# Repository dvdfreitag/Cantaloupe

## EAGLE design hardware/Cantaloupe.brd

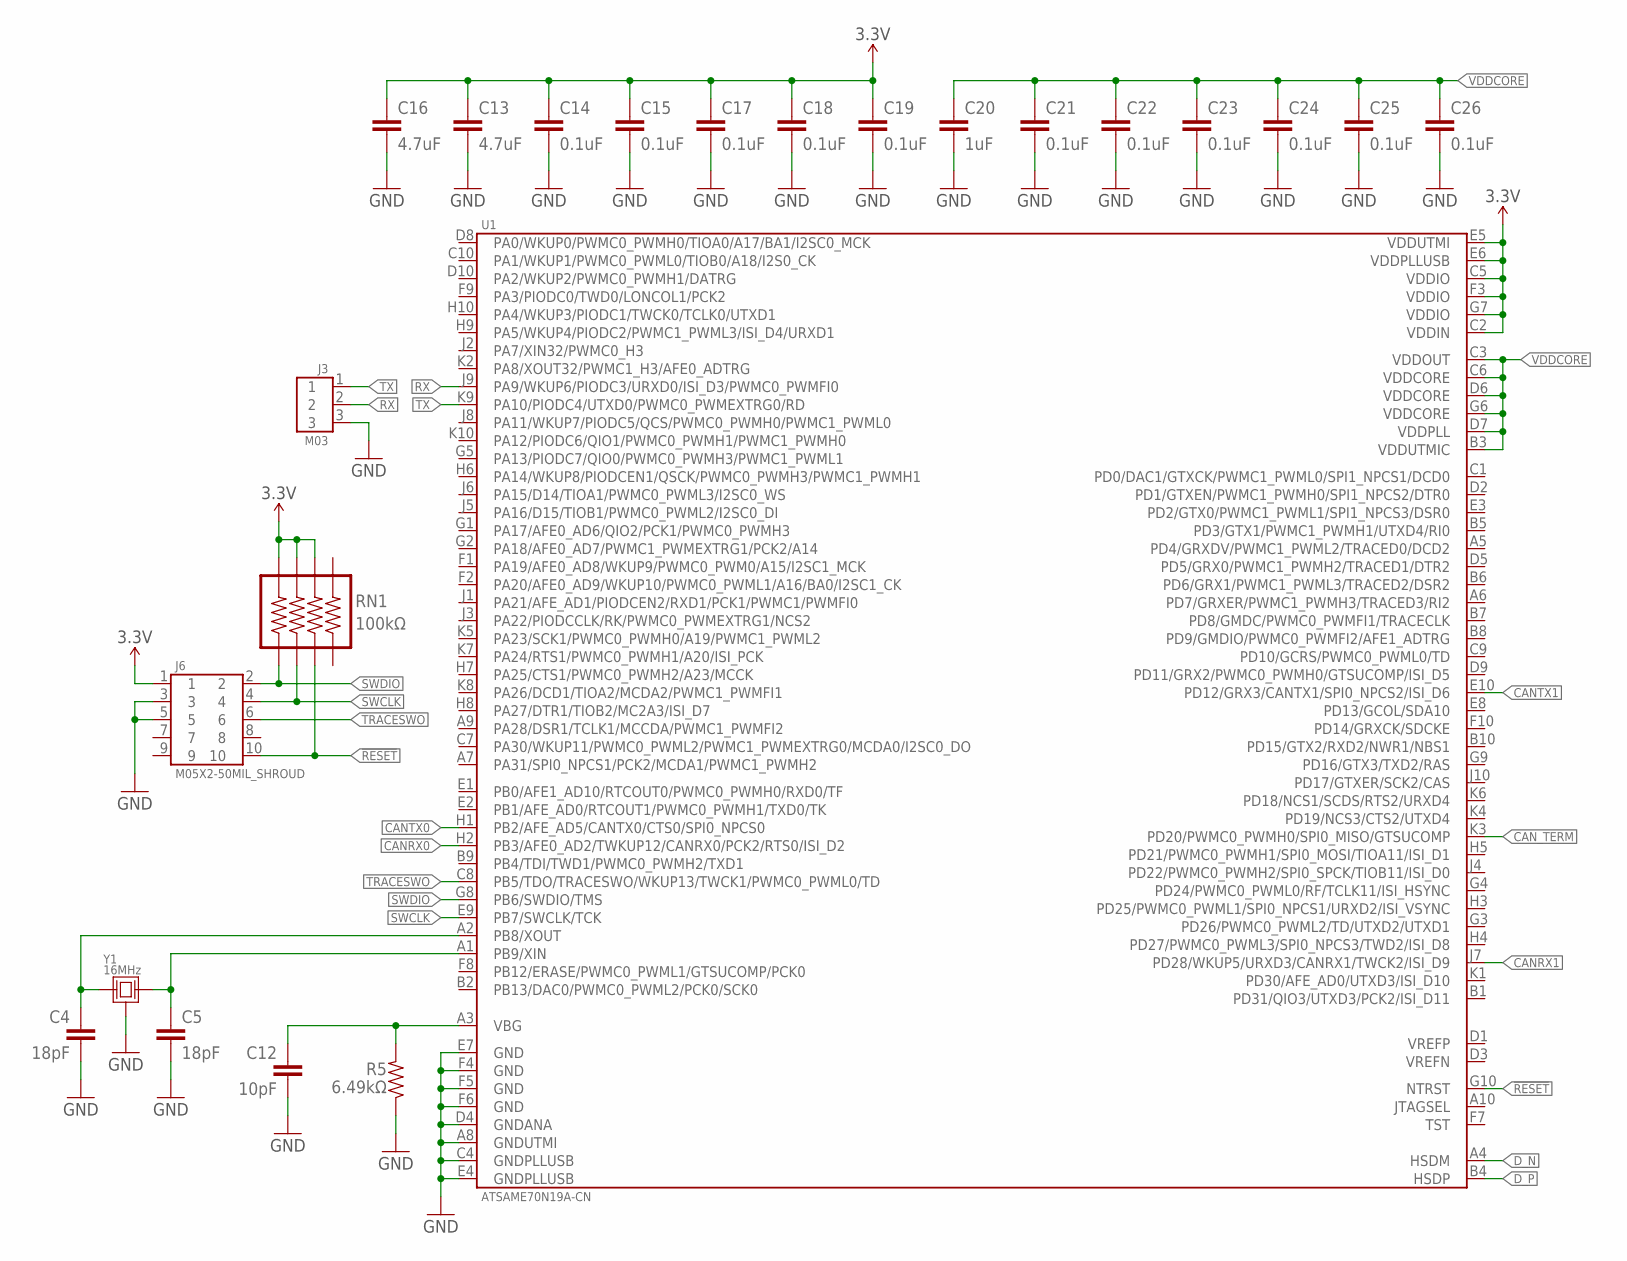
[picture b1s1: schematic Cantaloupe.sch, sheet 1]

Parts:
C4, C5: 18pF; 0603-CAP
C12: 10pF; 0603-CAP
C13, C16: 4.7uF; 0603-CAP
C14, C15, C17, C18, C19, C21, C22, C23, C24, C25, C26: 0.1uF; 0603-CAP
C20: 1uF; 0603-CAP
J3: M03
J6: M05X2-50MIL_SHROUD; M05X2-50MIL-SHROUD
R5: 6.49kΩ; 0603-CAP
RN1: 100kΩ; 1206-RESISTOR_ARRAY
U1: ATSAME70N19A-CN; TFBGA-100-9MM
Y1: 16MHz; FA-238

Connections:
3.3V: C13.1, C14.1, C15.1, C16.1, C17.1, C18.1, C19.1, J6.1, RN1.5, RN1.6, RN1.7, U1.C2 (VDDIN), U1.C5 (VDDIO), U1.E5 (VDDUTMI), U1.E6 (VDDPLLUSB), U1.F3 (VDDIO), U1.G7 (VDDIO); also elsewhere on the board
!RESET: J6.10, RN1.3, U1.G10 (NTRST)
CANRX0: U1.H2 (PB3/AFE0_AD2/TWKUP12/CANRX0/PCK2/RTS0/I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); also elsewhere on the board
CANRX1: U1.J7 (PD28/WKUP5/URXD3/CANRX1/TWCK2/ISI_D9); also elsewhere on the board
CANTX0: U1.H1 (PB2/AFE_AD5/CANTX0/CTS0/SPI0_NPCS0); also elsewhere on the board
CANTX1: U1.E10 (PD12/GRX3/CANTX1/SPI0_NPCS2/ISI_D6); also elsewhere on the board
CAN_TERM: U1.K3 (PD20/PWMC0_PWMH0/SPI0_MISO/GTSUCOMP); also elsewhere on the board
D_N: U1.A4 (HSDM); also elsewhere on the board
D_P: U1.B4 (HSDP); also elsewhere on the board
GND: C4.2, C5.2, C12.2, C13.2, C14.2, C15.2, C16.2, C17.2, C18.2, C19.2, C20.2, C21.2, C22.2, C23.2, C24.2, C25.2, C26.2, J3.3, J6.3, J6.5, R5.1, U1.A8 (GNDUTMI), U1.C4 (GNDPLLUSB), U1.D4 (GNDANA), U1.E4 (GNDPLLUSB), U1.E7 (GND), U1.F4 (GND), U1.F5 (GND), U1.F6 (GND), Y1.2 (GND), Y1.4 (GND); also elsewhere on the board
unnamed: C4.1, U1.A2 (PB8/XOUT), Y1.1
unnamed: C5.1, U1.A1 (PB9/XIN), Y1.3 (2)
unnamed: C12.1, R5.2, U1.A3 (VBG)
RX: J3.2, U1.J9 (PA9/WKUP6/PIODC3/URXD0/ISI_D3/PWMC0_PWM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)
SWCLK: J6.4, RN1.2, U1.E9 (PB7/SWCLK/TCK)
SWDIO: J6.2, RN1.1, U1.G8 (PB6/SWDIO/TMS)
TRACESWO: J6.6, U1.C8 (PB5/TDO/TRACESWO/WKUP13/TWCK1/PWMC0_PWM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)
TX: J3.1, U1.K9 (PA10/PIODC4/UTXD0/PWMC0_PWMEXTRG0/RD)
VDDCORE: C20.1, C21.1, C22.1, C23.1, C24.1, C25.1, C26.1, U1.B3 (VDDUTMIC), U1.C3 (VDDOUT), U1.C6 (VDDCORE), U1.D6 (VDDCORE), U1.D7 (VDDPLL), U1.G6 (VDDCORE)

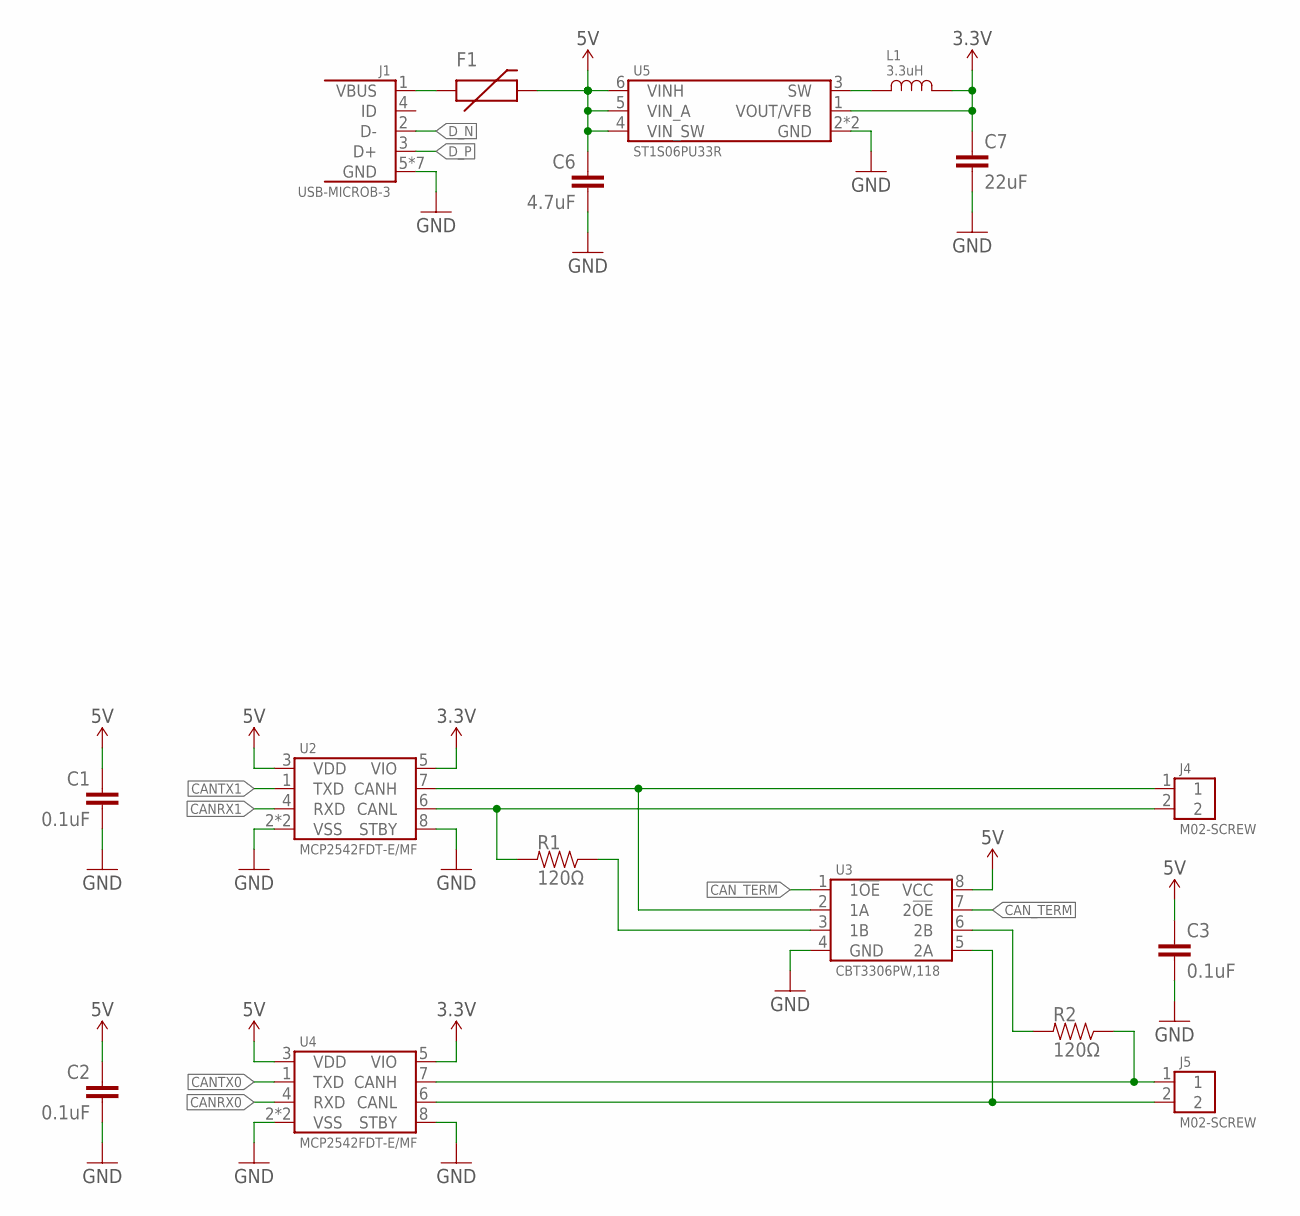
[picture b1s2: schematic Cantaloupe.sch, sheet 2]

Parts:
C1, C2, C3: 0.1uF; 0603-CAP
C6: 4.7uF; 0603-CAP
C7: 22uF; 1206
F1: PTC-1206; 1206-PTC
J1: USB-MICROB-3; 10118192-0001LF
J4, J5: M02-SCREW
L1: 3.3uH; 1008-INDUCTOR
R1, R2: 120Ω; 0603-CAP
U2, U4: MCP2542FDT-E/MF; DFN-8-3X3
U3: CBT3306PW,118; TSSOP8-4.4MM
U5: ST1S06PU33R; DFN-6-3MM

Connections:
3.3V: C7.1, L1.P$2, U2.5 (VIO), U4.5 (VIO), U5.1 (VOUT/VFB); also elsewhere on the board
5V: C1.1, C2.1, C3.1, C6.1, F1.P$2 (2), U2.3 (VDD), U3.8 (VCC), U4.3 (VDD), U5.4 (VIN_SW), U5.5 (VIN_A), U5.6 (VINH)
CANRX0: U4.4 (RXD); also elsewhere on the board
CANRX1: U2.4 (RXD); also elsewhere on the board
CANTX0: U4.1 (TXD); also elsewhere on the board
CANTX1: U2.1 (TXD); also elsewhere on the board
CAN_TERM: U3.1 (1!OE), U3.7 (2!OE); also elsewhere on the board
D_N: J1.2 (D-); also elsewhere on the board
D_P: J1.3 (D+); also elsewhere on the board
GND: C1.2, C2.2, C3.2, C6.2, C7.2, J1.5 (GND), J1.P$6 (GND), J1.P$7 (GND), J1.P$8 (GND), J1.P$9 (GND), J1.P$10 (GND), J1.P$11 (GND), U2.2 (VSS), U2.8 (STBY), U2.PAD (VSS), U3.4 (GND), U4.2 (VSS), U4.8 (STBY), U4.PAD (VSS), U5.2 (GND), U5.PAD (GND); also elsewhere on the board
unnamed: R1.1, U3.3 (1B)
unnamed: R2.2, U3.6 (2B)
unnamed: J4.1, U2.7 (CANH), U3.2 (1A)
unnamed: J4.2, R1.2, U2.6 (CANL)
unnamed: J5.1, R2.1, U4.7 (CANH)
unnamed: J5.2, U3.5 (2A), U4.6 (CANL)
unnamed: F1.P$1 (1), J1.1 (VBUS)
unnamed: L1.P$1, U5.3 (SW)

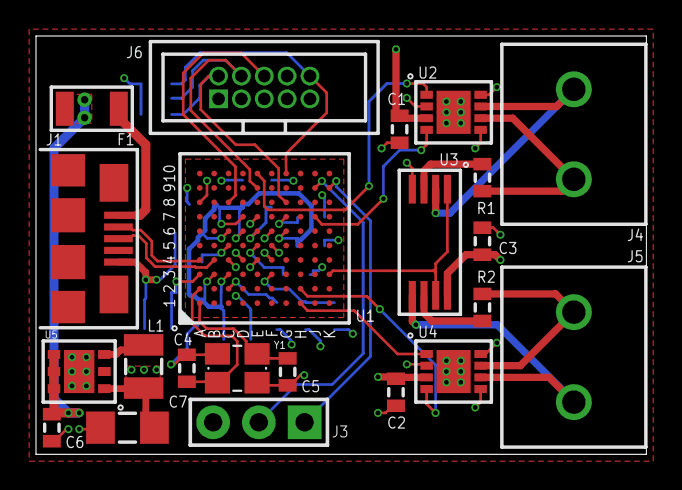
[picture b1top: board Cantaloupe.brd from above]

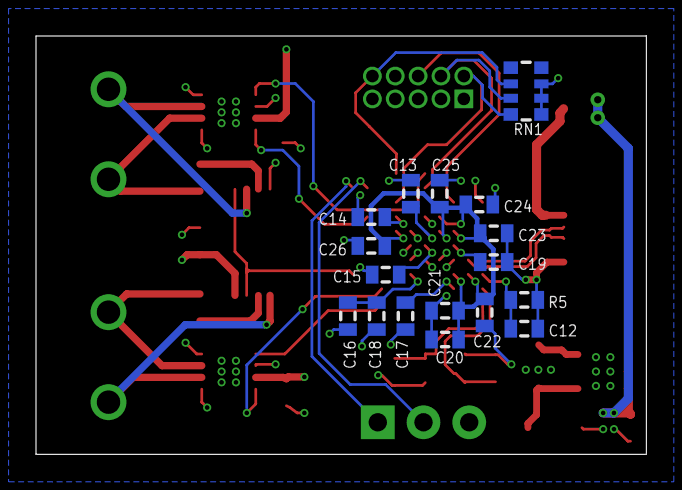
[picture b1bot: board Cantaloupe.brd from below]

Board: 4 copper layers, 33.9 x 23.2 mm, 39 parts (17 on the bottom side), 28 nets.

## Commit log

2017-05-21 Add license information
2017-05-21 Move readme
